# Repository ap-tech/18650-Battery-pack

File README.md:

# 18650-Battery-pack
This is a repository for making 18650 Battery packs. I will be making 3cell, 4cell, and 6cell. All packs will have inbuilt battery balancer from AliExpress I will also be looking at charging with just an off the shelf 24v power supply or transformer. The reason for this is so that you don't need to use "hard to come by" hobby modle chargers

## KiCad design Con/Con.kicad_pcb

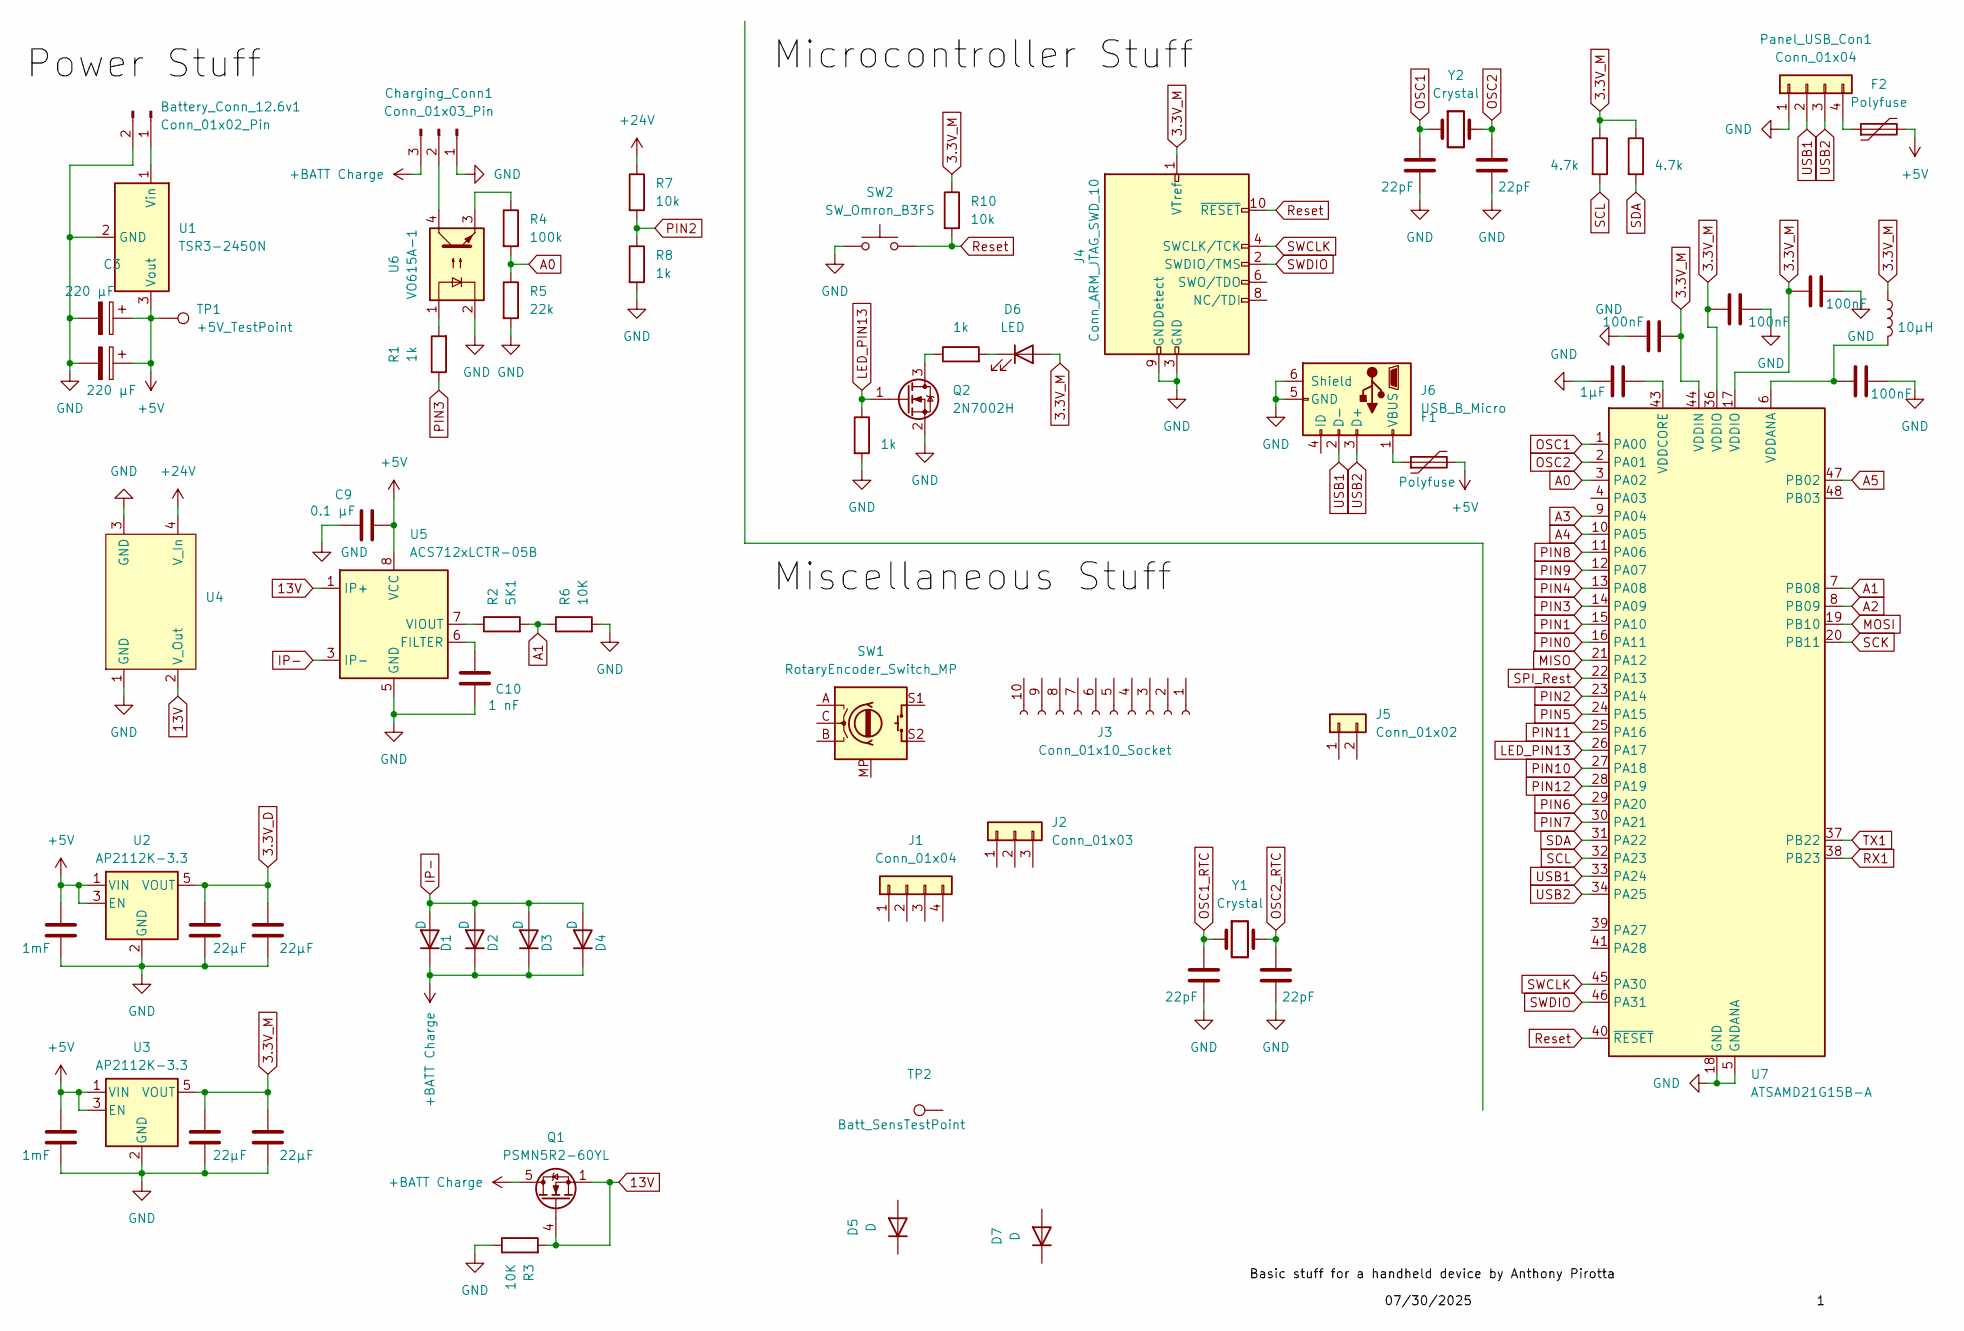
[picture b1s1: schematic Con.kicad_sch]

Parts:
Battery_Conn_12.6v1: Conn_01x02_Pin; PhoenixContact_MSTBA_2,5_2-G-5,08_1x02_P5.08mm_Horizontal
C1, C2: 1mF; C_0805_2012Metric_Pad1.18x1.45mm_HandSolder
C3, C4: 220 μF; CP_Radial_D6.3mm_P2.50mm
C5, C6, C7, C8: 22µF; C_0805_2012Metric_Pad1.18x1.45mm_HandSolder
C9: 0.1 μF; C_0805_2012Metric_Pad1.18x1.45mm_HandSolder
C10: 1 nF; C_0805_2012Metric_Pad1.18x1.45mm_HandSolder
C11, C12, C13, C14: 22pF; C_0805_2012Metric_Pad1.18x1.45mm_HandSolder
C15: 1µF; C_0805_2012Metric_Pad1.18x1.45mm_HandSolder
C16, C17, C18, C19: 100nF; C_0805_2012Metric_Pad1.18x1.45mm_HandSolder
Charging_Conn1: Conn_01x03_Pin; PhoenixContact_MSTBA_2,5_3-G-5,08_1x03_P5.08mm_Horizontal
D1, D2, D3, D4: D; D_PowerDI-5
D5, D7: D; D_QFN_3.3x3.3mm_P0.65mm
D6: LED; LED_0805_2012Metric
F1, F2: Polyfuse; C_1206_3216Metric
J1: Conn_01x04; Molex_KK-254_AE-6410-04A_1x04_P2.54mm_Vertical
J2: Conn_01x03; FanPinHeader_1x03_P2.54mm_Vertical
J3: Conn_01x10_Socket; Molex_SL_171971-0010_1x10_P2.54mm_Vertical
J4: Conn_ARM_JTAG_SWD_10; PinHeader_2x05_P1.27mm_Vertical
J5: Conn_01x02; Molex_KK-254_AE-6410-02A_1x02_P2.54mm_Vertical
J6: USB_B_Micro; 101181940001LF
L1: 10μH; L_0805_2012Metric
Panel_USB_Con1: Conn_01x04; Molex_KK-254_AE-6410-04A_1x04_P2.54mm_Vertical
Q1: PSMN5R2-60YL; LFPAK56
Q2: 2N7002H; SOT-23
R1, R8, R9, R11: 1k; R_0805_2012Metric
R2: 5K1; R_0805_2012Metric
R3, R6: 10K; R_0805_2012Metric
R4: 100k; R_0805_2012Metric
R5: 22k; R_0805_2012Metric
R7, R10: 10k; R_0805_2012Metric
R12, R13: 4.7k; R_0805_2012Metric
SW1: RotaryEncoder_Switch_MP; RotaryEncoder_Alps_EC12E-Switch_Vertical_H20mm
SW2: SW_Omron_B3FS; SW_Push_1P1T_NO_CK_KMR2
TP1: +5V_TestPoint; TestPoint_Pad_D2.5mm
TP2: Batt_SensTestPoint; TestPoint_Pad_D2.5mm
U1: TSR3-2450N; Converter_DCDC_TRACO_TSR2-24xxN_TSR2-24xxxN_THT
U2, U3: AP2112K-3.3; SOT-23-5
U4: DC_DC_Mod
U5: ACS712xLCTR-05B; SOIC-8_3.9x4.9mm_P1.27mm
U6: VO615A-1; SMDIP-4_W7.62mm
U7: ATSAMD21G15B-A; TQFP-48_7x7mm_P0.5mm
Y1, Y2: Crystal; Crystal_SMD_3215-2Pin_3.2x1.5mm

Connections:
3.3V_D: C5.1, C7.1, U2.5 (VOUT)
3.3V_M: C6.1, C8.1, C16.1, C17.1, C18.1, D6.2 (A), J4.1 (VTref), L1.1, R10.1, R12.1, R13.1, U3.5 (VOUT), U7.17 (VDDIO), U7.36 (VDDIO), U7.44 (VDDIN)
13V: Q1.1 (S), Q1.2 (S), Q1.3 (S), Q1.4 (G), R3.2, U4.2 (V_Out), U5.1 (IP+), U5.2 (IP+)
+5V: C1.1, C2.1, C3.1, C4.1, C9.2, F1.2, F2.2, TP1.1, U1.3 (Vout), U2.1 (VIN), U2.3 (EN), U3.1 (VIN), U3.3 (EN), U5.8 (VCC)
+24V: R7.1, U4.4 (V_In)
+BATT Charge: Charging_Conn1.3, D1.1 (K), D2.1 (K), D3.1 (K), D4.1 (K), Q1.5 (D)
A0: R4.2, R5.1, U7.3 (PA02)
A1: R2.2, R6.1, U7.7 (PB08)
A2: U7.8 (PB09)
A3: U7.9 (PA04)
A4: U7.10 (PA05)
A5: U7.47 (PB02)
GND: Battery_Conn_12.6v1.2, C1.2, C2.2, C3.2, C4.2, C5.2, C6.2, C7.2, C8.2, C9.1, C10.2, C11.2, C12.2, C13.2, C14.2, C15.1, C16.2, C17.2, C18.2, C19.2, Charging_Conn1.1, J4.3 (GND), J4.5 (GND), J4.9 (GNDDetect), J6.5 (GND), J6.6 (Shield), Panel_USB_Con1.1, Q2.2 (S), R3.1, R5.2, R6.2, R8.2, R9.2, SW2.1, U1.2 (GND), U2.2 (GND), U3.2 (GND), U4.1 (GND), U4.3 (GND), U5.5 (GND), U6.2, U7.5 (GNDANA), U7.18 (GND), U7.35 (GND), U7.42 (GND)
IP-: D1.2 (A), D2.2 (A), D3.2 (A), D4.2 (A), U5.3 (IP-), U5.4 (IP-)
LED_PIN13: Q2.1 (G), R9.1, U7.26 (PA17)
MISO: U7.21 (PA12)
MOSI: U7.19 (PB10)
unnamed: Battery_Conn_12.6v1.1, U1.1 (Vin)
unnamed: Charging_Conn1.2, U6.4
unnamed: D6.1 (K), R11.2
unnamed: F1.1, J6.1 (VBUS)
unnamed: F2.1, Panel_USB_Con1.4
unnamed: Q2.3 (D), R11.1
unnamed: R1.2, U6.1
unnamed: R4.1, U6.3
unnamed: C10.1, U5.6 (FILTER)
unnamed: R2.1, U5.7 (VIOUT)
unnamed: C19.1, L1.2, U7.6 (VDDANA)
unnamed: C15.2, U7.43 (VDDCORE)
OSC1: C13.1, U7.1 (PA00), Y2.1
OSC1_RTC: C11.1, Y1.1
OSC2: C14.1, U7.2 (PA01), Y2.2
OSC2_RTC: C12.1, Y1.2
PIN0: U7.16 (PA11)
PIN1: U7.15 (PA10)
PIN2: R7.2, R8.1, U7.23 (PA14)
PIN3: R1.1, U7.14 (PA09)
PIN4: U7.13 (PA08)
PIN5: U7.24 (PA15)
PIN6: U7.29 (PA20)
PIN7: U7.30 (PA21)
PIN8: U7.11 (PA06)
PIN9: U7.12 (PA07)
PIN10: U7.27 (PA18)
PIN11: U7.25 (PA16)
PIN12: U7.28 (PA19)
RX1: U7.38 (PB23)
Reset: J4.10 (~RESET), R10.2, SW2.2, U7.40 (~RESET)
SCK: U7.20 (PB11)
SCL: R12.2, U7.32 (PA23)
SDA: R13.2, U7.31 (PA22)
SPI_Rest: U7.22 (PA13)
SWCLK: J4.4 (SWCLK/TCK), U7.45 (PA30)
SWDIO: J4.2 (SWDIO/TMS), U7.46 (PA31)
TX1: U7.37 (PB22)
USB1: J6.2 (D-), Panel_USB_Con1.2, U7.33 (PA24)
USB2: J6.3 (D+), Panel_USB_Con1.3, U7.34 (PA25)

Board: 2 copper layers, 66 parts (0 on the bottom side), 36 nets, no tracks yet.

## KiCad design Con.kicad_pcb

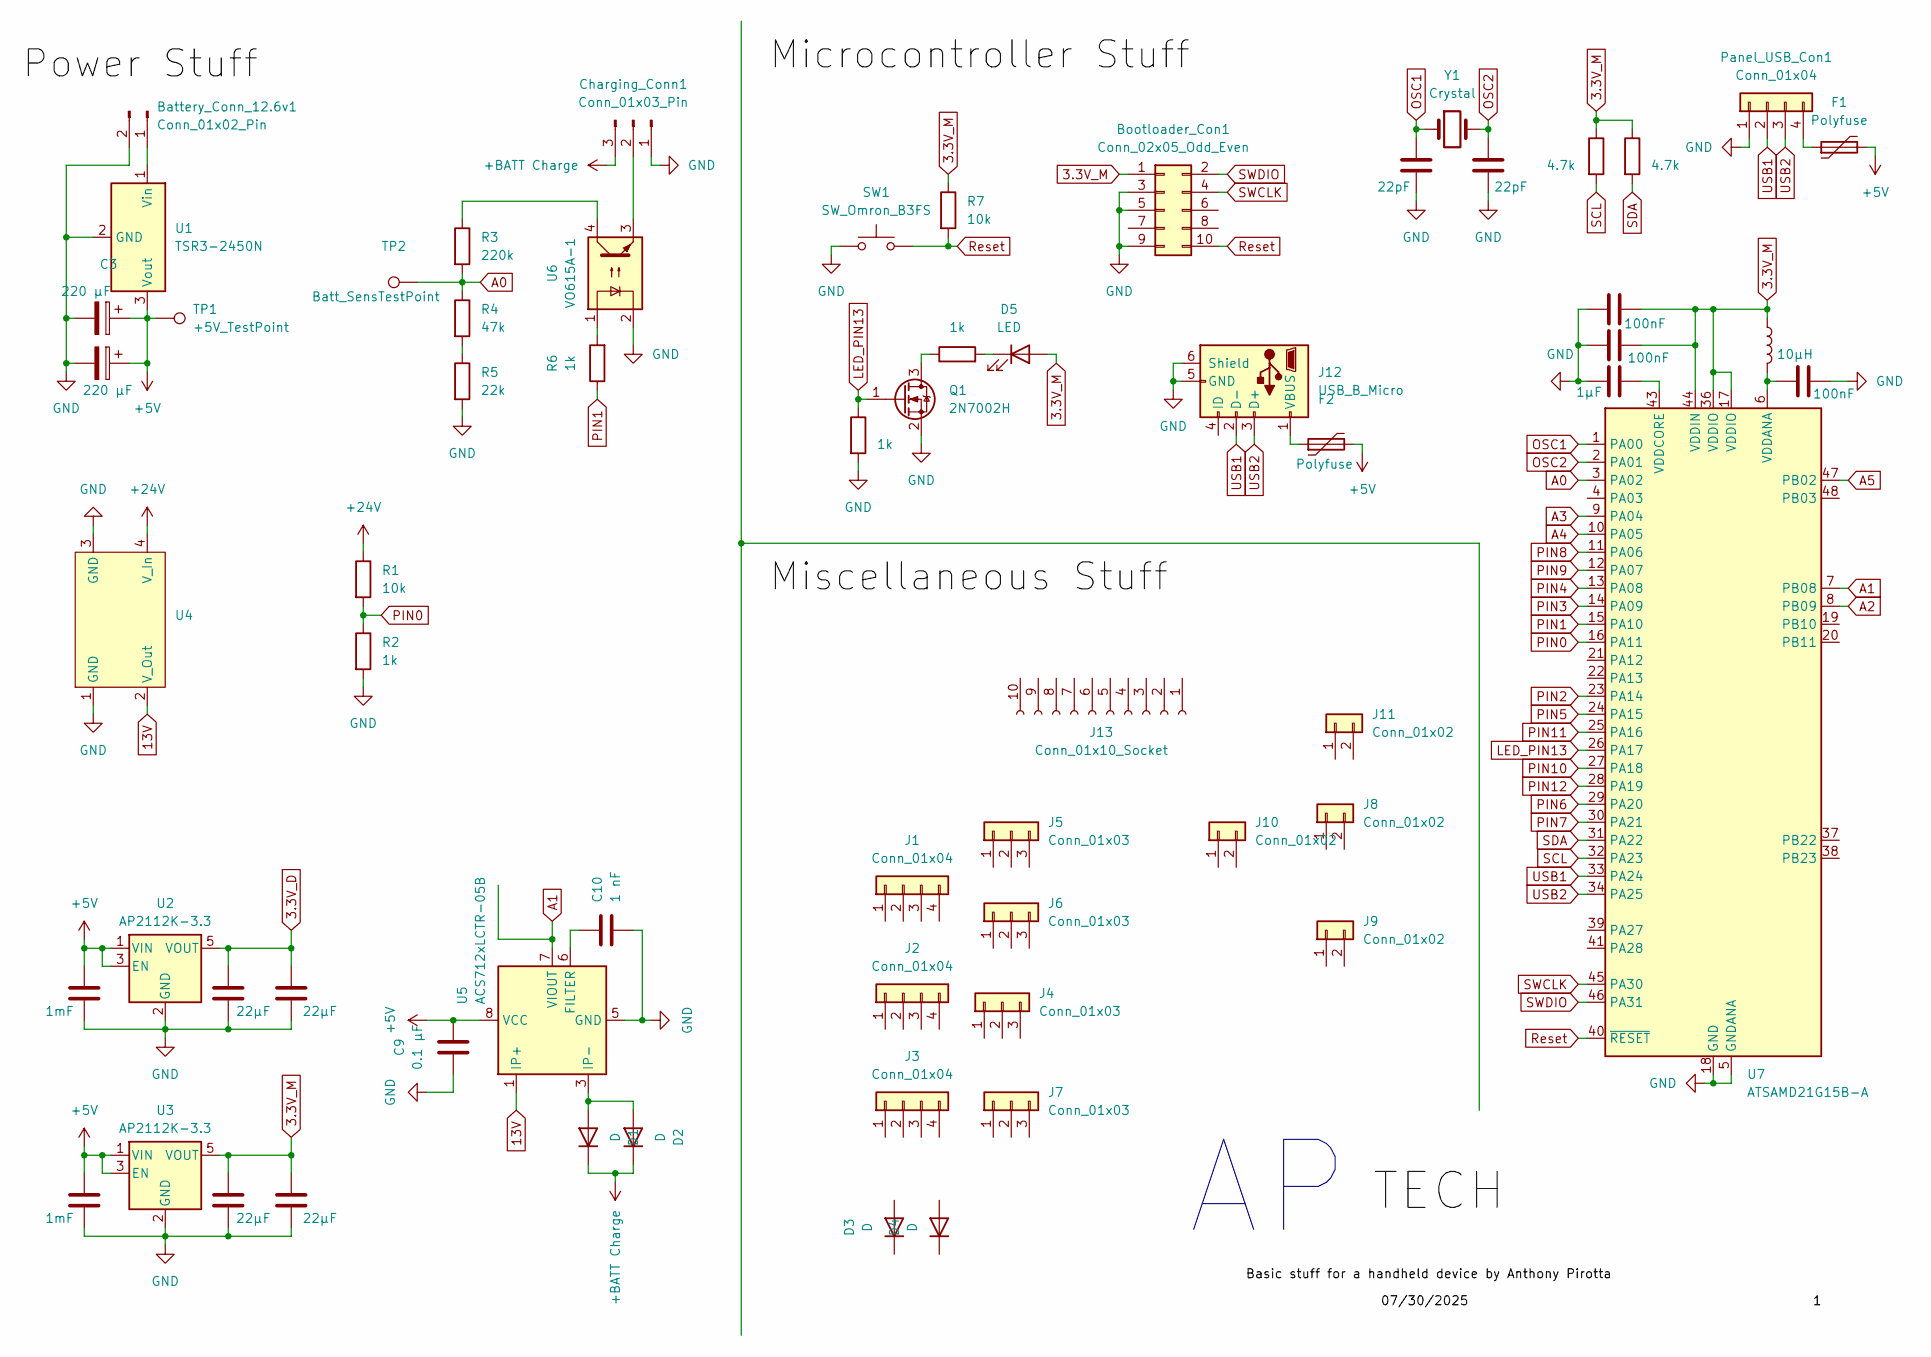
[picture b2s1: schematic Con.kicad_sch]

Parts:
Battery_Conn_12.6v1: Conn_01x02_Pin; PhoenixContact_MSTBA_2,5_2-G-5,08_1x02_P5.08mm_Horizontal
Bootloader_Con1: Conn_02x05_Odd_Even; PinHeader_2x05_P1.00mm_Vertical
C1, C2: 1mF; C_0805_2012Metric_Pad1.18x1.45mm_HandSolder
C3, C4: 220 μF; CP_Radial_D6.3mm_P2.50mm
C5, C6, C7, C8: 22µF; C_0805_2012Metric_Pad1.18x1.45mm_HandSolder
C9: 0.1 μF; C_0805_2012Metric_Pad1.18x1.45mm_HandSolder
C10: 1 nF; C_0805_2012Metric_Pad1.18x1.45mm_HandSolder
C11, C12, C13: 100nF; C_0805_2012Metric_Pad1.18x1.45mm_HandSolder
C14: 1µF; C_0805_2012Metric_Pad1.18x1.45mm_HandSolder
C15, C16: 22pF; C_0805_2012Metric_Pad1.18x1.45mm_HandSolder
Charging_Conn1: Conn_01x03_Pin; PhoenixContact_MSTBA_2,5_3-G-5,08_1x03_P5.08mm_Horizontal
D1, D2: D; D_PowerDI-5
D3, D4: D; D_QFN_3.3x3.3mm_P0.65mm
D5: LED; LED_0805_2012Metric
F1, F2: Polyfuse; C_1206_3216Metric
J1, J2, J3: Conn_01x04; Molex_KK-254_AE-6410-04A_1x04_P2.54mm_Vertical
J4, J5, J6, J7: Conn_01x03; FanPinHeader_1x03_P2.54mm_Vertical
J8, J9, J10, J11: Conn_01x02; Molex_KK-254_AE-6410-02A_1x02_P2.54mm_Vertical
J12: USB_B_Micro; 101181940001LF
J13: Conn_01x10_Socket; Molex_SL_171971-0010_1x10_P2.54mm_Vertical
L1: 10μH; L_0805_2012Metric
Panel_USB_Con1: Conn_01x04; Molex_KK-254_AE-6410-04A_1x04_P2.54mm_Vertical
Q1: 2N7002H; SOT-23
R1, R7: 10k; R_0805_2012Metric
R2, R6, R11, R12: 1k; R_0805_2012Metric
R3: 220k; R_0805_2012Metric
R4: 47k; R_0805_2012Metric
R5: 22k; R_0805_2012Metric
R9, R10: 4.7k; R_0805_2012Metric
SW1: SW_Omron_B3FS; SW_Push_1P1T_NO_CK_KMR2
TP1: +5V_TestPoint; TestPoint_Pad_D2.5mm
TP2: Batt_SensTestPoint; TestPoint_Pad_D2.5mm
U1: TSR3-2450N; Converter_DCDC_TRACO_TSR2-24xxN_TSR2-24xxxN_THT
U2, U3: AP2112K-3.3; SOT-23-5
U4: DC_DC_Mod
U5: ACS712xLCTR-05B; SOIC-8_3.9x4.9mm_P1.27mm
U6: VO615A-1; SMDIP-4_W7.62mm
U7: ATSAMD21G15B-A; TQFP-48_7x7mm_P0.5mm
Y1: Crystal; Crystal_SMD_3215-2Pin_3.2x1.5mm

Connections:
3.3V_D: C5.1, C7.1, U2.5 (VOUT)
3.3V_M: Bootloader_Con1.1, C6.1, C8.1, C11.2, C12.2, D5.2 (A), L1.1, R7.1, R9.1, R10.1, U3.5 (VOUT), U7.17 (VDDIO), U7.36 (VDDIO), U7.44 (VDDIN)
13V: U4.2 (V_Out), U5.1 (IP+), U5.2 (IP+)
+5V: C1.1, C2.1, C3.1, C4.1, C9.2, F1.2, F2.2, TP1.1, U1.3 (Vout), U2.1 (VIN), U2.3 (EN), U3.1 (VIN), U3.3 (EN), U5.8 (VCC)
+24V: R1.1, U4.4 (V_In)
+BATT Charge: Charging_Conn1.3, D1.1 (K), D2.1 (K)
A0: R3.2, R4.1, TP2.1, U7.3 (PA02)
A1: U5.7 (VIOUT), U7.7 (PB08)
A2: U7.8 (PB09)
A3: U7.9 (PA04)
A4: U7.10 (PA05)
A5: U7.47 (PB02)
GND: Battery_Conn_12.6v1.2, Bootloader_Con1.3, Bootloader_Con1.5, Bootloader_Con1.9, C1.2, C2.2, C3.2, C4.2, C5.2, C6.2, C7.2, C8.2, C9.1, C10.2, C11.1, C12.1, C13.2, C14.1, C15.2, C16.2, Charging_Conn1.1, J12.5 (GND), J12.6 (Shield), Panel_USB_Con1.1, Q1.2 (S), R2.2, R5.2, R11.2, SW1.1, U1.2 (GND), U2.2 (GND), U3.2 (GND), U4.1 (GND), U4.3 (GND), U5.5 (GND), U6.2, U7.5 (GNDANA), U7.18 (GND), U7.35 (GND), U7.42 (GND)
LED_PIN13: Q1.1 (G), R11.1, U7.26 (PA17)
unnamed: Battery_Conn_12.6v1.1, U1.1 (Vin)
unnamed: Charging_Conn1.2, U6.3
unnamed: D1.2 (A), D2.2 (A), U5.3 (IP-), U5.4 (IP-)
unnamed: D5.1 (K), R12.2
unnamed: F2.1, J12.1 (VBUS)
unnamed: F1.1, Panel_USB_Con1.4
unnamed: Q1.3 (D), R12.1
unnamed: R3.1, U6.4
unnamed: R4.2, R5.1
unnamed: R6.2, U6.1
unnamed: C10.1, U5.6 (FILTER)
unnamed: C13.1, L1.2, U7.6 (VDDANA)
unnamed: C14.2, U7.43 (VDDCORE)
OSC1: C15.1, U7.1 (PA00), Y1.1
OSC2: C16.1, U7.2 (PA01), Y1.2
PIN0: R1.2, R2.1, U7.16 (PA11)
PIN1: R6.1, U7.15 (PA10)
PIN2: U7.23 (PA14)
PIN3: U7.14 (PA09)
PIN4: U7.13 (PA08)
PIN5: U7.24 (PA15)
PIN6: U7.29 (PA20)
PIN7: U7.30 (PA21)
PIN8: U7.11 (PA06)
PIN9: U7.12 (PA07)
PIN10: U7.27 (PA18)
PIN11: U7.25 (PA16)
PIN12: U7.28 (PA19)
Reset: Bootloader_Con1.10, R7.2, SW1.2, U7.40 (~RESET)
SCL: R9.2, U7.32 (PA23)
SDA: R10.2, U7.31 (PA22)
SWCLK: Bootloader_Con1.4, U7.45 (PA30)
SWDIO: Bootloader_Con1.2, U7.46 (PA31)
USB1: J12.2 (D-), Panel_USB_Con1.2, U7.33 (PA24)
USB2: J12.3 (D+), Panel_USB_Con1.3, U7.34 (PA25)

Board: 2 copper layers, 64 parts (0 on the bottom side), 34 nets, no tracks yet.

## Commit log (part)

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2025-03-09 Add files via upload
    18650 Battery Pack jigs for 3cell 4cell and 6cell.
2025-07-31 Create Charger_PCB
